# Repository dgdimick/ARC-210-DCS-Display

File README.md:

# ARC-210 Radio Control Panel for DCS A-10C II using a 3.5" SPI TFT display and DCS-BIOS — November 14, 2026

**Last updated: November 14, 2026 at 1:36 AM MST (America/Denver)**

**[Windows COM port tools](Tools/README.md)** — Download the scripts to rename a COM port in Device Manager or restore its previous display name.

I’m building a working ARC-210 radio panel for the DCS A-10C II using a Teensy 4.1, a 3.5-inch ILI9488 TFT display, custom PCBs, and 3D-printed parts, with DCS-BIOS for live radio data and cockpit control. I’m sharing the files and what I learn along the way so you can build your own.

I spend about **8 hours a day on my SIMPIT projects**, including working on the code, PCB design, assembly, and test fitting.

**Frequency controls:** I use **rotary encoders** for the frequency controls in this build, rather than the **ten-position rotary switches used in the real ARC-210**. **For Version 2, I plan to replace the five frequency encoders with rotary switches and mount the existing Main Board lower behind the panel.** See [Future thoughts and plans](Docs/Future-Thoughts.md) for the planned redesign; there is no release date yet.

## [Assembly Instructions](Docs/Build%20Guide/README.md)

Have all the parts and ready to build it?

## Current testing status

**The panel is now working connected to DCS.** [Watch the demonstration video](https://drive.google.com/file/d/1jLG8JLaTQ1RpAE6FKkDZAUxiwgUSQEKu/view?usp=drivesdk). The manufactured PCBs have arrived. The assembled Rotary Switch PCBs v2.0 passed both fit and functional testing. Assembly and testing continue on the rest of the panel.

**Assembly testing:** Use the [Final Hardware Test](Firmware/Test%20Code/ARC210_Button_Test/README.md). The individual TFT, button, encoder, and switch tests are optional troubleshooting tools; you don’t need to run them during normal assembly.

**What to expect before radio data arrives:**

- **v0.1.3 Diagnostic HEX:** The display stays on the splash screen while waiting for radio data. This is expected and does not mean the Teensy has frozen.
- **v0.1.2 Preview HEX:** The display stays blank until DCS-BIOS sends powered-radio data.

[See the official DCS website](https://www.digitalcombatsimulator.com/en/)

> **Note:** This repository is now included in the [A-10-Sim repository](https://github.com/dgdimick/A-10-Sim).

## Features

[View the features](Docs/Features.md) for the hardware capabilities and planned firmware support.

## Items that need to be completed

**Last updated: November 13, 2026 at 2:15 AM MST (America/Denver)**

[View the remaining work](Docs/Remaining-Work.md) for the testing, documentation, and design tasks still to complete.

**SQL On/Off:** I use the **C&K A12515RNZQ solder-lug rotary switch**, with its stop ring set to **two positions for 45° total travel**. Align the knob with the panel’s ON/OFF markings. See the [parts list](parts/README.md) for shaft-length and mounting details.

## Tools needed

[View the tools needed](Docs/Tools-Needed.md) to build and program the panel.

## Future thoughts and plans

**Future upgrades:** It may be as long as **two years** before I return to this project with upgrades or a new version. Please treat future-version ideas as long-term plans, with no promised release date.

[View Future thoughts and plans](Docs/Future-Thoughts.md) for possible redesigns, lighting, and support for other aircraft.

**The current Button Matrix PCB v3.2 does not support LED backlighting.** For a V2 upgrade I plan four boards total: the existing Main Board mounted lower, a new three-FREQ/CHANNEL board, a new two-FREQ board with SQL On/Off and 5 V lighting power, and a new backlit Button Matrix Board. I'll reuse the Teensy 4.1 and keep the existing TFT wiring. I plan to buy five new FREQ rotary switches and one new CHANNEL encoder, and reuse MODE and MASTER if they fit. The cost of either V2 path makes it a very low priority for me. I'll finish C-130J support before I even look at V2. **Version 2 is a long way off, so please don't wait for it if you want to build the ARC-210.** For a new V2 build, I plan three boards by combining the two-FREQ power board with a redesigned Main Board. See [both V2 board layouts](Docs/Future-Thoughts.md#version-2-board-layout).

## Project updates

**Last updated: November 13, 2026 at 1:54 AM MST (America/Denver)**

**November 13, 2026 at 1:54 AM MST — Windows COM port rename and restore scripts complete**

The optional Windows scripts let you give any connected device listed under Ports (COM & LPT) a display name of your choice in Device Manager. The rename script adds the existing COM number to your label, and the restore script puts the previous label back. The default example uses a Teensy on COM5 and labels it **ARC-210 (COM5)**. Enter the COM port Windows assigned to your device and the name you want it changed to. I tested both scripts on that Teensy and on a Bluetooth serial device on COM3. I still need to check live DCS-BIOS communication after renaming the port on the flight sim PC. [USB naming how-to](Tools/README.md)

[Read all project updates](Docs/Project-Updates.md) for the full dated development history.

## Bare PCB offer

I can provide **bare PCBs only**, not a kit of electronic components or an assembled panel. See my [ARC-210 bare PCB offer](Docs/ARC-210-Parts-Offers.md#bare-pcb-set) for the boards included, availability, shipping, and fees. My bare PCB offer covers the ARC-210. I’ll offer printing help for the ARC-164 and ARC-186 once their printed parts are finalized. I’m happy to provide a free printed set whether you get your PCBs from me or elsewhere. Just cover shipping.

## No access to a 3D printer?

I offer separate 3D-printing help for builders who can’t build the panel because they don’t have access to a 3D printer. This supplies printed plastic only, not electronic components or a complete kit; buy the other components separately. The complete set of 3D-printed parts is free on request. Just cover shipping. See [ARC-210 3D-printing help](Docs/ARC-210-Parts-Offers.md#printed-parts) for materials, colors, availability, shipping, VAT, and import charges.

## My SIMPIT and test computer

[View my SIMPIT and test computer](Docs/My-SIMPIT-and-Test-Computer.md) for my computer configuration, monitors, and current USB setup.

## USB connections and powered hubs

[Read about the USB connection plan and purchased powered hubs](Docs/USB-Connections-and-Powered-Hubs.md) for why I am using USB instead of RS-485.

I also own three other SIMPIT panels that use USB. I have used them for over **1,000 hours in the past year without any issues**.

I plan to use this [Veeloon Micro-USB male to USB-C female adapter cable](https://www.amazon.com/dp/B0G5YZJLVZ?th=1) with the Teensy 4.1 to provide an accessible USB-C connection. The listing specifies a **0.6 ft (about 183 mm)** cable and **480 Mbps data transfer**. **On my ARC-210, I used this adapter to control the panel through DCSBridge and successfully program the Teensy.** I still need to test it in live DCS and verify that it reconnects reliably after unplugging it.

### ARC-210 USB name in Windows

Use the [optional Windows USB display name utility](Tools/README.md) to rename the port in Device Manager or restore its previous label.

[Download the ARC-210 USB name test HEX v.1](Firmware/Master%20Hex%20Files/ARC210_A-10C2_USB-Name_Test_v.1.hex) and flash it with Teensy Loader. I verified the USB name on Windows. DCS-BIOS communication with this test build is still pending.

The v0.1.6 Control Test for Teensy 4.1 adds the **ARC-210** USB product name to the v0.1.5 control firmware. It compiled successfully and is available for panel testing. [Download the v0.1.6 Control Test HEX](Firmware/Master%20Hex%20Files/ARC210_A-10C2_v0.1.6_Control_Test_Teensy41.hex).

I verified that the ARC-210 USB name test HEX reports **ARC-210** as its USB product name. In Device Manager, open **Ports (COM & LPT)**, right-click the panel's COM port, and select **Properties → Details → Bus reported device description** to see it.

The registry change below is optional. Without it, Device Manager will typically list the panel as **USB Serial Device (COM5)** under **Ports (COM & LPT)**, using whichever COM number Windows assigns. With the v0.1.6 HEX loaded, **Properties → Details → Bus reported device description** will show **ARC-210**. The registry change makes the Ports list show **ARC-210 (COM5)**. Teensy programming and DCS-BIOS communication work with either display name.

If I move the panel to another computer, Windows may assign it a different COM number. Select the new port in TekConnect. With firmware that reports **ARC-210**, the USB product name stays on the Teensy, and its hardware serial number normally stays the same. The custom Device Manager label is saved on each Windows computer, so renaming the port again is **optional**. The panel can be programmed and used with DCS-BIOS using the default Windows label.

I set the Windows display name to **ARC-210 (COM5)** on my PC. To do the same, open **Windows PowerShell** with **Run as administrator** and run the commands below. If your panel is on a different port, change `COM5` in the first line. The commands check that the connected device reports **ARC-210** before renaming it.

```powershell
$port = 'COM5'
$devices = @(Get-PnpDevice -PresentOnly -Class Ports -ErrorAction Stop |
    Where-Object {
        $_.FriendlyName -like "*($port)" -and
        $_.InstanceId -like 'USB\VID_16C0*'
    })
if ($devices.Count -ne 1) { throw "Expected one Teensy on $port." }

$device = $devices[0]
$product = Get-PnpDeviceProperty -InstanceId $device.InstanceId `
    -KeyName DEVPKEY_Device_BusReportedDeviceDesc -ErrorAction Stop
if ($product.Data -ne 'ARC-210') { throw "$port does not report ARC-210." }

$key = 'HKLM:\SYSTEM\CurrentControlSet\Enum\' + $device.InstanceId
Set-ItemProperty -LiteralPath $key -Name FriendlyName -Value "ARC-210 ($port)" -ErrorAction Stop
Get-PnpDevice -InstanceId $device.InstanceId | Select-Object FriendlyName, Status
```

Reopen Device Manager if it still shows the old label. The display name applies to that device instance on the Windows PC where you ran the commands.

## DCS-BIOS

[My step-by-step setup guide](Docs/DCS-BIOS.md) covers installation, file changes, and TekConnect—the app I use to manage my connections.

- [Patched A-10C.lua](https://raw.githubusercontent.com/dgdimick/ARC-210-DCS-Display/master/Docs/DCS-BIOS/A-10C.lua) — ARC-210 changes included; for **DCS-BIOS v0.11.8**.
- [DCS-BIOS-only Export.lua](https://raw.githubusercontent.com/dgdimick/ARC-210-DCS-Display/master/Docs/DCS-BIOS/DCS-BIOS-only/Export.lua) — for setups without WWT or SRS.

Follow the guide before replacing files.

## [Estimated total build cost](parts/README.md#estimated-total-build-cost)

## [Why I used a Teensy](Docs/Why-Teensy.md)

## Firmware and hardware information

[Firmware and hardware information](Docs/Firmware-and-Hardware-Information.md) for wiring, power, PCB layout, parts, printable files, software, firmware loading, and testing guides.

## Project progress and beta testing

[View project progress and beta testing](Docs/Project-Progress-and-Beta-Testing.md) for the progress video and information on helping test the panel.

## [Sharing code and improvements](Firmware/README.md)

## Questions and community builds

If you’d like to build an ARC-210 but aren’t able to assemble it yourself, get in touch through [Discussions](https://github.com/dgdimick/ARC-210-DCS-Display/discussions). I’d be happy to talk about your situation and see how I can help.

**Planning a build, already working on one, or just looking around?** [Introduce yourself in the welcome discussion](https://github.com/dgdimick/ARC-210-DCS-Display/discussions/1) and tell me which panel interests you and what you fly. Questions, ideas, and progress photos are welcome—even if you haven’t started yet.

I’m sharing the files and build notes to help you make your own panel, with parts available from the linked suppliers. If you get stuck, ask in [GitHub Discussions](https://github.com/dgdimick/ARC-210-DCS-Display/discussions)—I’m happy to help where I can.

If you’re local to me in **New Mexico, USA**, I’d be happy to meet up and provide whatever help I can with your SIMPIT. Get in touch through [Discussions](https://github.com/dgdimick/ARC-210-DCS-Display/discussions) so we can talk about your build and arrange a time.

I welcome bug reports from anyone using the project—**even tiny bugs are worth reporting**. If something doesn’t work as expected, please let me know in the [Bugs discussion section](https://github.com/dgdimick/ARC-210-DCS-Display/discussions/categories/bugs). Tell me which firmware version and board revision you’re using, if applicable, what you did, what you expected, and what happened. Reports about the build instructions are welcome too. Your reports help me improve the project for everyone.

## Related radio projects

I’m finishing the A-10C II ARC-210 first, then the ARC-164 and ARC-186, before returning to additional aircraft support. [My development priorities](Docs/Related-Radio-Projects.md) may change based on feedback and interest.

I’m developing [C-130J ARC-210 support](Docs/C-130J-Support.md) here in the main project. The same ARC-210 hardware should work with both the **A-10C II and C-130J**, through a shared code base with automatic aircraft selection and aircraft-specific DCS-BIOS mappings, without reflashing the Teensy when switching aircraft. This support, including C-130J operation, still needs to be implemented and tested.

[Explore the ARC-164 and ARC-186 projects and planned C-130J ARC-210 support](Docs/Related-Radio-Projects.md) for project updates and build plans.

## PC Flights affiliation

I am not affiliated with [PC Flights](https://pcflights.com/) in any way. I simply chose to use their panels for my own cockpit projects. PC Flights has supplied me with a drawing file to assist with the Button PCB layout.

## Disclaimer

This is a hobby flight-simulation project, not equipment intended for use in real aircraft. Software, firmware, PCB designs, wiring information, and printable parts are provided "as is," without warranty, subject to their respective licenses.

Users are responsible for verifying compatibility, wiring, supply voltages, assembly, and safe operation before use. To the maximum extent permitted by applicable law, the authors and contributors disclaim liability for injury, equipment damage, data loss, or other losses arising from use of this project.

## Licensing

- **PCBs:** CERN Open Hardware Licence Version 2 - Permissive (CERN-OHL-P-2.0)
- **Teensy firmware:** MIT License
- **STL files:** Creative Commons Attribution 4.0 International (CC BY 4.0)

See the `Docs` directory for copies of the applicable licenses.

---

[**My Mission Statement — Why I Build and Share These Projects**](https://github.com/dgdimick/A-10-Sim/blob/master/Mission-Statement.md)

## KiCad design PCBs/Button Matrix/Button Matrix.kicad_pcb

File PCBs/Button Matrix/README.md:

# ARC-210 Button Matrix PCB

**Last updated: November 13, 2026 at 9:41 PM MST (America/Denver)**

**October 30, 2026 — v3.2 released:** Removed the duplicate approximately 13.38 mm Edge.Cuts circle at H3; the intended opening remains a **12.0 mm non-plated hole**. Board and schematic revisions and the silkscreen are now **3.2**. I moved H3’s reference label clear of the hole’s solder-mask opening. There are no electrical changes. Gerbers and drills were freshly exported with KiCad 10.0.7; fresh ERC/DRC checks report zero violations, zero unconnected items, and zero schematic/PCB mismatches under the saved settings. Use the [v3.2 manufacturing ZIP](Manufacturing/Button-Matrix-PCB-v3.2-Gerbers-Drill.zip) for new orders.

Current Main Board version: **1.1**.

PCB version **3.2 — SQL clearance-hole correction**. The outer outline and button positions retain the v3.1 physical-fit check; manufactured v3.2 assembly and electrical testing remain pending.

Updated October 30, 2026. The current PCB, schematic, project settings, and project-local footprint library are included in this folder.

This is the current **unlit 16-button, 4 × 4 matrix**.

**The current Button Matrix PCB v3.2 does not support LED backlighting.** I would need to redesign the button board with LED support, use suitable light-transmitting buttons, and make the required Main Board, power, and driver changes. I may revisit this after completing the ARC-164 and ARC-186 projects; there is no finished backlit button-board design or release date yet. See [Future Thoughts](../../Docs/Future-Thoughts.md) for the lighting redesign plan.

**SQL On/Off:** I use the **C&K A12515RNZQ solder-lug rotary switch**, with its stop ring set to **two positions for 45° total travel**. Align the knob with the panel’s ON/OFF markings. See the [parts list](../../parts/README.md) for shaft-length and mounting details.

## Download and open

Use **Code → Download ZIP** on the repository, extract it, and keep this folder together. Open `Button Matrix.kicad_pro` in KiCad 10, then open the schematic or PCB Editor. The [schematic](Button%20Matrix.kicad_sch) and [PCB layout](Button%20Matrix.kicad_pcb) are also available directly.

The design uses standard KiCad `Connector`, `Device`, `Switch`, and `Mechanical` symbols. Install KiCad’s standard libraries and keep `fp-lib-table` and `ButtonMatrix.pretty/` beside the project. The local library supplies H3’s 12 mm non-plated SQL On/Off switch pass-through footprint.

**PCB version 3.2:** The saved PCB includes placement and routing. I removed unused floating copper fills on October 27, 2026. I shortened the slightly long board edges and checked the button positions with a printed fit test. Testing an assembled manufactured board remains pending. A [Gerber and drill ZIP](Manufacturing/Button-Matrix-PCB-v3.2-Gerbers-Drill.zip) is included for manufacturing.

## Gerber and drill files

Download [Button-Matrix-PCB-v3.2-Gerbers-Drill.zip](Manufacturing/Button-Matrix-PCB-v3.2-Gerbers-Drill.zip) for a PCB manufacturer. Generated October 30, 2026 from the corrected version 3.2 PCB using KiCad 10.0.7.

The ZIP contains the seven Gerber X2 layers (front/back copper, solder mask, silkscreen, and board outline), a Gerber job file, separate metric Excellon PTH/NPTH drill files, and manufacturing notes. Both Gerbers and drills use the absolute origin without mirroring. The source specifies a two-layer, 1.6 mm board.

The exports were checked against the source: **130 plated holes and five non-plated holes**, including four 3.5 mm mounting holes and H3’s 12 mm SQL On/Off pass-through. [Individual files, drill maps, and drill report](Manufacturing/) are also available. Before you order, check the board outline, center opening, and hole placement in the manufacturer's preview. The printed fit check confirmed button alignment; manufactured-board assembly and electrical testing remain pending.

**Final v3.1 design; test fit confirmed — October 27, 2026:** I physically test-fitted the revised v3.1 board, and it fits. The buttons are in the correct locations. The board edges were slightly too long and have been shortened for version **3.1**, which preceded the v3.2 hole correction. This historical fit check applies to the unchanged outer outline and button positions; use v3.2 for new orders. The obsolete v3.0 manufacturing ZIP has been removed; Git history retains earlier revisions.

## SQL On/Off switch shaft support

The [shaft spacer v.5](../../Supporting%20STL%27s/Shaft_Spacer_v.5.stl) is **required in all installations** to support the **longer SQL On/Off switch shaft**. Fit it whether using the optional SQL On/Off PCB or wiring directly to the switch’s solder lugs. H3’s 12 mm opening in the Button Matrix PCB provides pass-through clearance for the SQL On/Off switch.

## Layout reference pictures

These front and back pictures show the earlier **v3.0** layout. The current v3.2 files retain the slightly shortened v3.1 board edges; use the current KiCad layout and manufacturing files for exact dimensions. The large opening is the SQL On/Off switch pass-through.

### Front — push-button switches

### Back — diodes and connectors

**The switches go on the front side of the PCB, facing the faceplate. The diodes and pin connectors go on the opposite (back) side.** The silkscreen markings show which side each component belongs on, so check those markings before soldering.

**Photo reminder for my next assembly:** Once the manufactured PCBs arrive and I start building, I’ll add front-and-back photos here showing the switches on the front and the diodes and pin connectors on the back, with the silkscreen markings visible.

## Trim front-side leads before mounting

**Solder the diodes first.** Install the sixteen 1N4148 diodes (D5–D20) on the back of the PCB. Match each diode’s band (cathode) to the silkscreen before soldering.

On the front, use flush cutters to trim the diode leads as close to the PCB as you can without cutting into the pads. If a joint needs a touch-up after trimming, briefly touch it with a clean soldering iron tip to reflow the existing solder. It should leave a small, low bead around the lead so the PCB can sit flush behind the faceplate.

**Solder the J1 and J2 pin headers on the back before installing the buttons.** Then solder the tactile switches on the front. Trim any protruding header pins on the front and clear away the clippings before mounting the PCB.

<p align="center">
  
</p>

*Front of my Button Matrix PCB after trimming the diode leads and pin-header pins. Click the photo to view it full size.*

## Buttons and connectors

Use 16 SPST momentary tactile switches, **6 × 6 × 5 mm**, with four through-hole leads. See the [parts list and supplier](../../parts/README.md#current-button-switches). Confirm the purchased switches’ contact pairing and footprint before fabrication. Verify the supplied footprint against your purchased switches before fabrication.

The schematic has **two separate four-pin connectors**, rather than one eight-pin connector:

| Button Matrix connector | Main Board J2 pin | Teensy GPIO label | KiCad Teensy U1 pad |
| --- | ---: | ---: | ---: |
| J1 pin 1 — row 1 | 1 | 30 | 22 |
| J1 pin 2 — row 2 | 2 | 31 | 23 |
| J1 pin 3 — row 3 | 3 | 32 | 24 |
| J1 pin 4 — row 4 | 4 | 33 | 25 |
| J2 pin 1 — column 1 | 5 | 35 | 27 |
| J2 pin 2 — column 2 | 6 | 36 | 28 |
| J2 pin 3 — column 3 | 7 | 37 | 29 |
| J2 pin 4 — column 4 | 8 | 40 | 32 |

The connector reference J2 on this button schematic is different from J2 on the Main Board. Use the table to wire between them. The supplied PCB uses these two four-pin connectors.

**Teensy printed GPIO labels differ from KiCad pad numbers.** For example, GPIO 30 is U1 pad 22. Use the Teensy labels for firmware and wiring, and the matching symbol/footprint pad numbers when working in KiCad.

## Diodes and testing

D5–D20 are the 16 matrix diodes. Their cathodes connect to the row lines. Confirm the intended 1N4148 parts, polarity, and supplied footprints before fabrication. See the [parts documentation](../../parts/README.md).

The [combined hardware test](../../Firmware/Test%20Code/ARC210_Button_Test/) documents the working matrix GPIO assignments and button tests. A successful breadboard test does not establish that the final PCB design has been assembled or tested.

KiCad 10.0.7 checks run October 27, 2026 reported **zero ERC violations, zero DRC errors, zero unconnected items, and zero schematic/PCB parity issues** under the saved settings. After removal of the unused no-net copper fills, DRC reports **zero warnings**. The board has no ground net and does not require a ground plane. See the [ERC summary](ERC-report.txt) and [DRC report](DRC-report.json). Some check categories are disabled. Button alignment was verified with the printed fit check; electrical operation of an assembled manufactured board has not yet been tested.

## Lighting

The PC Flights panel buttons used for this build are painted and opaque, so light will not pass through them to illuminate their legends. This design has no button-lighting LEDs.

**The current Button Matrix PCB v3.2 does not support LED backlighting.** I would need to redesign it and the Main Board and use light-transmitting buttons. There is no finished design or release date. The TFT backlight is separate; see [Future Thoughts](../../Docs/Future-Thoughts.md) for clearance, power, possible four-layer costs, and reusable-part plans.

My aim for a future LED upgrade is to let builders reuse the **rotary encoders, rotary switches, socket-mounted Teensy, and faceplate**, along with other compatible parts outside the replacement Main Board and button board. I still need to confirm compatibility during the redesign. Using male headers on the Teensy and matching female sockets on the Main Board would let you move the controller to a compatible replacement board and save buying another one. See [Future Thoughts](../../Docs/Future-Thoughts.md) for the upgrade plans.

## No access to a 3D printer?

I offer separate 3D-printing help for builders whose lack of printer access is preventing their build. This supplies printed plastic only, not electronic components or a complete kit; buy the other components separately. See [ARC-210 3D-printing help](../../Docs/ARC-210-Parts-Offers.md#printed-parts) for the current price, PETG colors, availability, shipping, VAT, and import-charge details.

## Build cost and community

See the [DIY parts purchasing estimate](../../parts/README.md#estimated-build-cost) for a build budget. Parts and fabrication are sourced independently; this is primarily a DIY project.

Need a hand? Ask in [Discussions](https://github.com/dgdimick/ARC-210-DCS-Display/discussions), share your build photos, or [introduce yourself](https://github.com/dgdimick/ARC-210-DCS-Display/discussions/1).

PCB design license: CERN-OHL-P-2.0, as specified in the [main README](../../README.md#licensing).

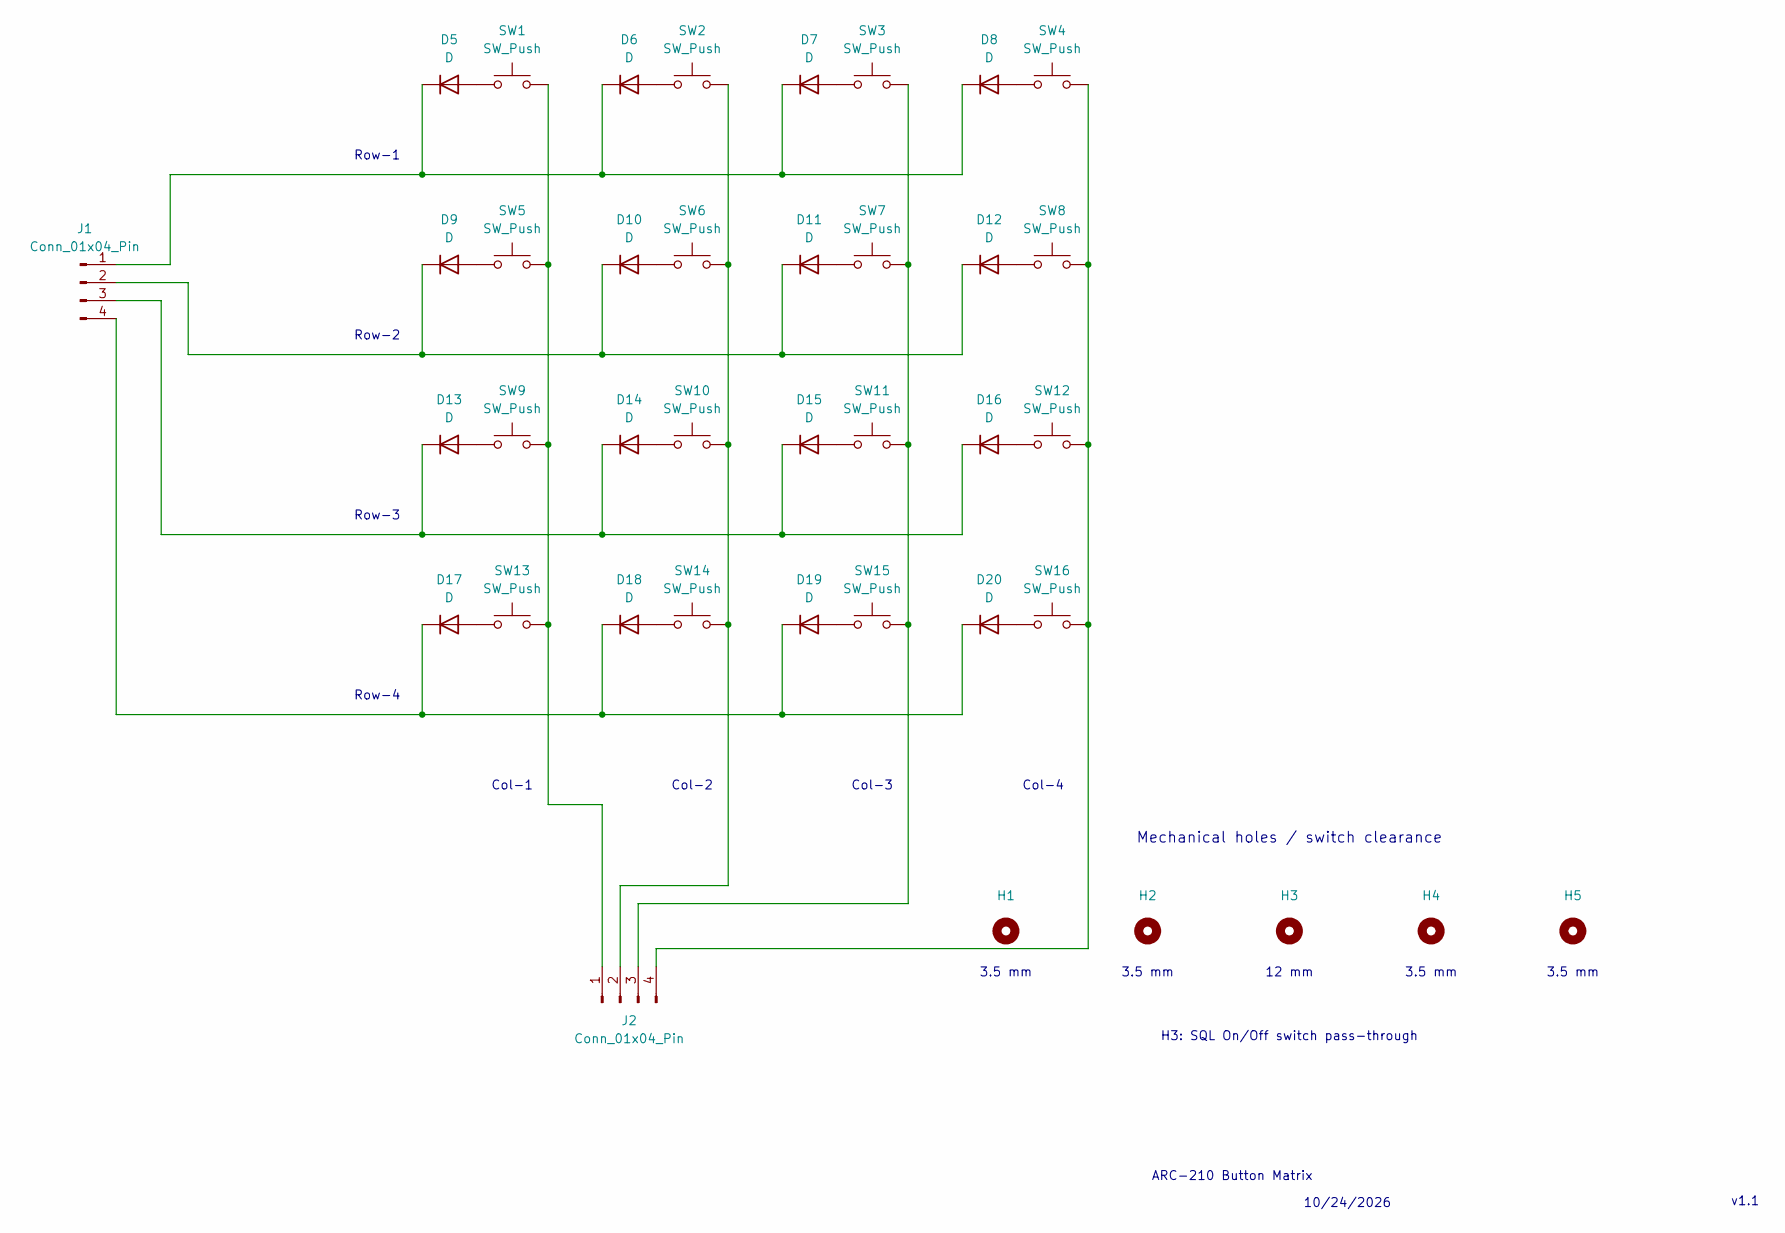
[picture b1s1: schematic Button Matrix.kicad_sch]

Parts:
D5, D6, D7, D8, D9, D10, D11, D12, D13, D14, D15, D16, D17, D18, D19, D20: D; D_DO-35_SOD27_P7.62mm_Horizontal
H1, H2, H4, H5: MountingHole_3.5mm
H3: MountingHole_12mm
J1, J2: Conn_01x04_Pin; PinHeader_1x04_P2.54mm_Vertical
SW1, SW2, SW3, SW4, SW5, SW6, SW7, SW8, SW9, SW10, SW11, SW12, SW13, SW14, SW15, SW16: SW_Push; SW_PUSH_6mm

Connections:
unnamed: D5.2 (A), SW1.1
unnamed: D5.1 (K), D6.1 (K), D7.1 (K), D8.1 (K), J1.1
unnamed: D6.2 (A), SW2.1
unnamed: D7.2 (A), SW3.1
unnamed: D8.2 (A), SW4.1
unnamed: D9.2 (A), SW5.1
unnamed: D10.2 (A), SW6.1
unnamed: D9.1 (K), D10.1 (K), D11.1 (K), D12.1 (K), J1.2
unnamed: D11.2 (A), SW7.1
unnamed: D12.2 (A), SW8.1
unnamed: D13.2 (A), SW9.1
unnamed: D13.1 (K), D14.1 (K), D15.1 (K), D16.1 (K), J1.3
unnamed: D14.2 (A), SW10.1
unnamed: D15.2 (A), SW11.1
unnamed: D16.2 (A), SW12.1
unnamed: D17.2 (A), SW13.1
unnamed: D17.1 (K), D18.1 (K), D19.1 (K), D20.1 (K), J1.4
unnamed: D18.2 (A), SW14.1
unnamed: D19.2 (A), SW15.1
unnamed: D20.2 (A), SW16.1
unnamed: J2.1, SW1.2, SW5.2, SW9.2, SW13.2
unnamed: J2.2, SW2.2, SW6.2, SW10.2, SW14.2
unnamed: J2.3, SW3.2, SW7.2, SW11.2, SW15.2
unnamed: J2.4, SW4.2, SW8.2, SW12.2, SW16.2

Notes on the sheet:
ARC-210 Button Matrix
10/24/2026
Row-4
Col-2
Row-2
Col-4
Col-1
Row-3
v1.1
Row-1
Col-3
Mechanical holes / switch clearance
3.5 mm
12 mm
H3: SQL On/Off switch pass-through

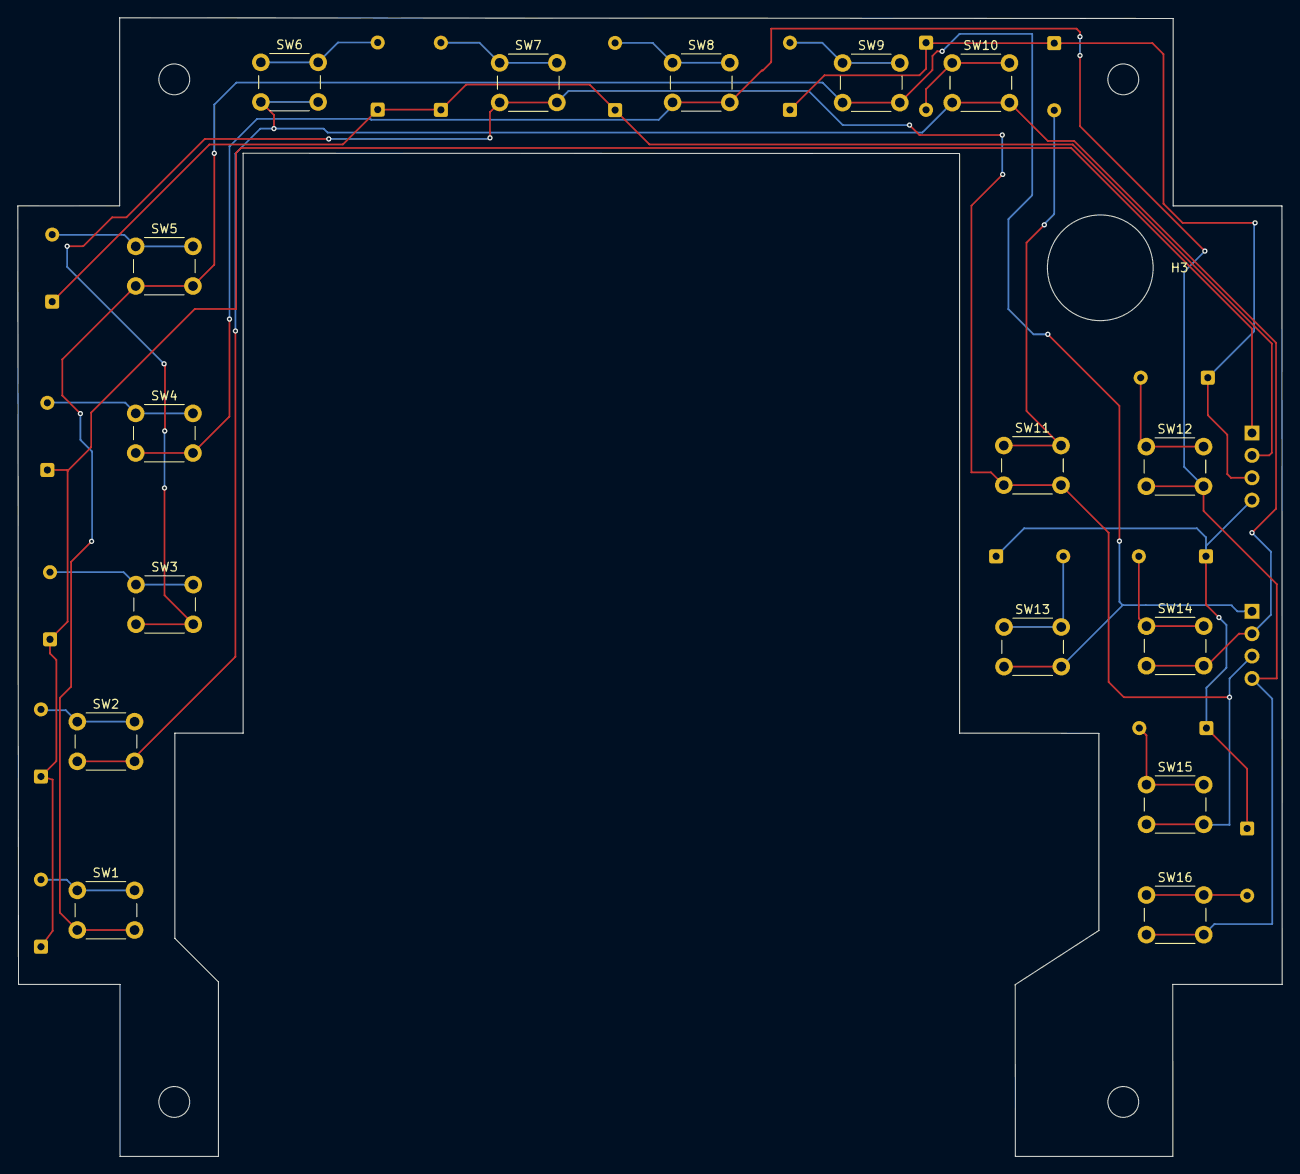
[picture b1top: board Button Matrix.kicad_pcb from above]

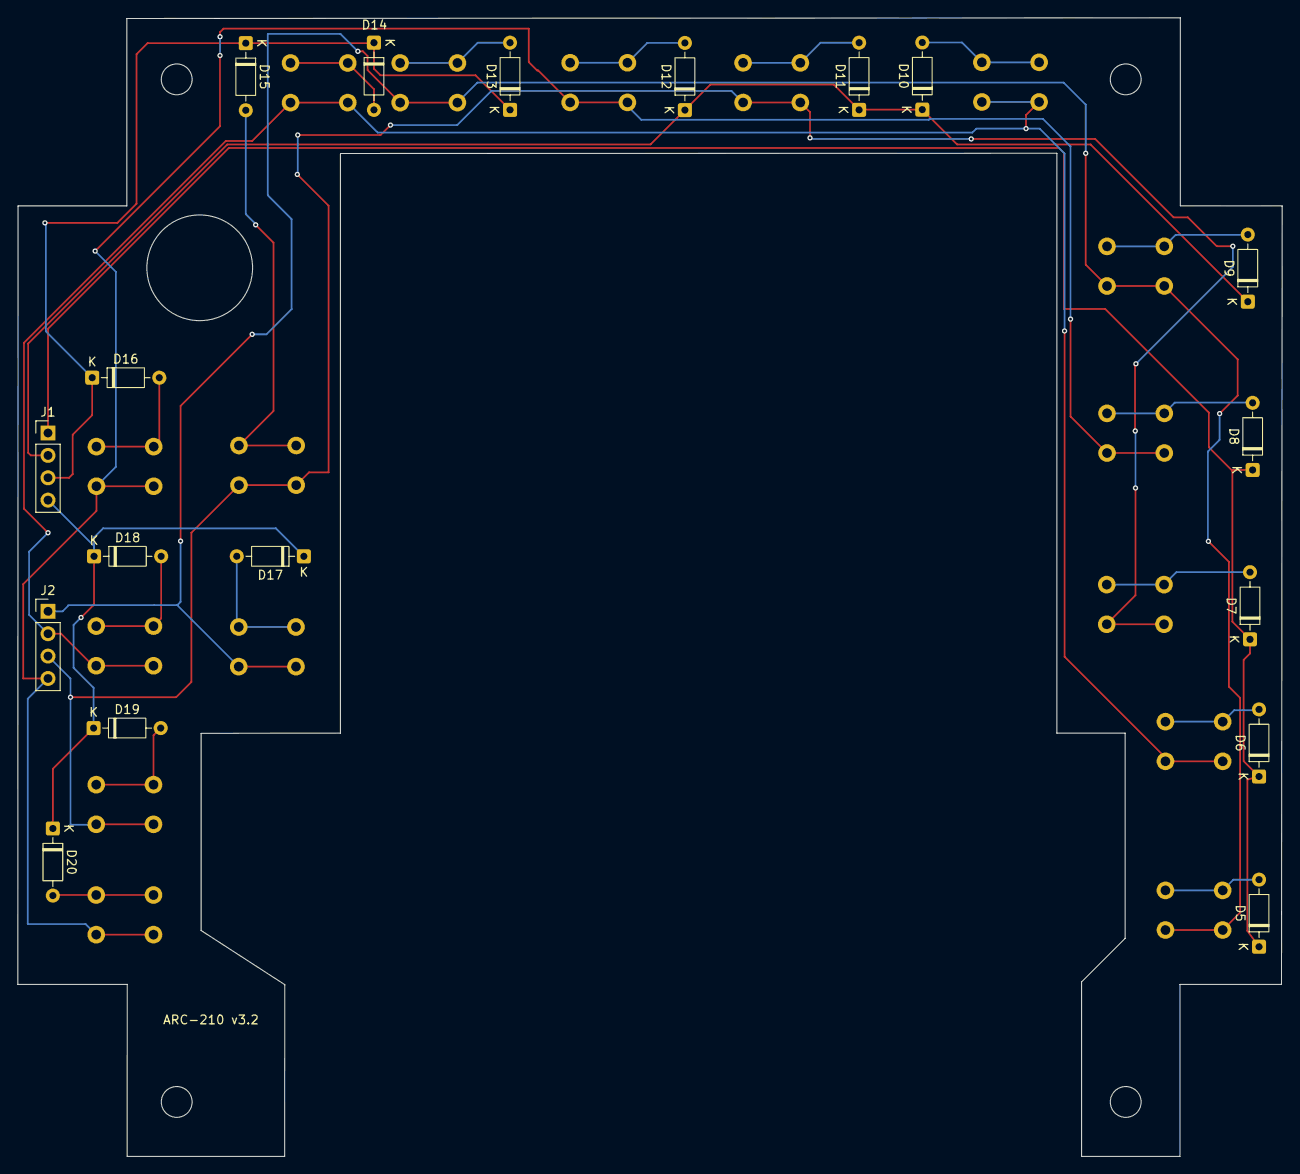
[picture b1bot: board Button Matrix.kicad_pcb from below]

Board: 2 copper layers, 143.5 x 129.2 mm, 39 parts (18 on the bottom side), 24 nets.
